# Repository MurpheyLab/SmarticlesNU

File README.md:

# SmarticlesNU

This repository includes all the hardware design and software files for the smarticle system. Examples can be found in Code/Python/Examples. See [Smarticle Tracking](https://github.com/murpheylab/SmarticleTracking) for the a python AprilTag tracking library and [SmarticleSimulation](https://github.com/asamland/SmarticleSimulation) for a PyBullet simulator of the system.  

All documentation for the python modules in this repository is available [here](https://murpheylab.github.io/SmarticlesNU/)

Installing Python Dependencies
------------

You can install pyserial and the XBee Python library using pip

    $ pip install pyserial
    $ pip install digi-xbee

Running Your First Program
-----------
Use the included `SmarticleSyncGait.py` to test your setup. You will have to modify `PORT_NAME` to match the USB port name of the local XBee connected to your computer.  

Run the the following command to execute the code and keep the python script open  
    
    $ python3 -i SmarticleSyncGait.py
    
Then you can run this command to run the smarticles for 1 minute  

    >>> timed_sync(1)

Interfacing with The Xbees
---
To Change the settings of the Base Xbee, use [DIGI XCTU](https://www.digi.com/resources/documentation/digidocs/90001526/tasks/t_download_and_install_xctu.htm)  
The Settings for the base Xbee are the default settings for 802.15.4 firmware with these changes:  
<br>
        **1.** Change mode (AP) to API Enabled  
        **2.** Change Pan ID (ID) to 1984  
        **3.** Ensure address (MY) is 0  
        **4.** Change Destination Low Address (DL) to 0xFFFF (broadcast)  
        
You can also modify these settings in a simple serial console by entering command mode. See this [guide](https://cdn.sparkfun.com/learn/materials/29/22AT%20Commands.pdf) for more information.
    
Modifying Code on The Smarticles
---
To modify the code on the smarticles themselves, you will also need to instal MiniCore into the Arduino IDE and an SI Labs driver for the CP2104 chip.  
  <br> 
    Get the CP210x Driver for your OS: [SI Labs Drivers Link](https://www.silabs.com/products/interface/usb-bridges/classic-usb-bridges/device.cp2104?q=cp2104;page=1;x6=searchHeader;q6=Software)  
    Download Arduino IDE: [Arduino IDE Link](https://www.arduino.cc/en/Main/Software)  
    Follow the instructions to install in Arduino IDE: [MiniCore Link](https://github.com/MCUdude/MiniCore#how-to-install) 
    <br>
    
After Installing all these dependencies you will have to move the files from the Code/Arduino folder into your local Arduino folder (usually found in documents)  
<br>
        **1.**  Move the programmable_smarticle folder into your Arduino directory (should be then documents/Arduino/programmable_smarticle)  
        **2.**  Move the contents of the repo Arduino/libraries folder into your local Arduino/libraries folder  
    
You will have to restart the Arduino IDE and then you should be able to open the programmable_smarticle.ino sketch and you should see PWMServo, NeoHWSerial, and Smarticle in the Sketch->Include Library file menu.

To upload the program to the smarticle, use the follow board configuration under the tools file menu:  

  | Field | Value|
|:------------:|:-------------------------------:| 
| Board        | ATmega328                      | 
| Clock        | 8MHz External                   |  
| BOD          | BOD 2.7V                        |  
| Compiler LTO | LTO Enabled                     |  
| Variant      | 328PB                           |  
| Bootloader   | Yes (UART0)                     |  
| Port         | select USB port of SI Labs Chip |

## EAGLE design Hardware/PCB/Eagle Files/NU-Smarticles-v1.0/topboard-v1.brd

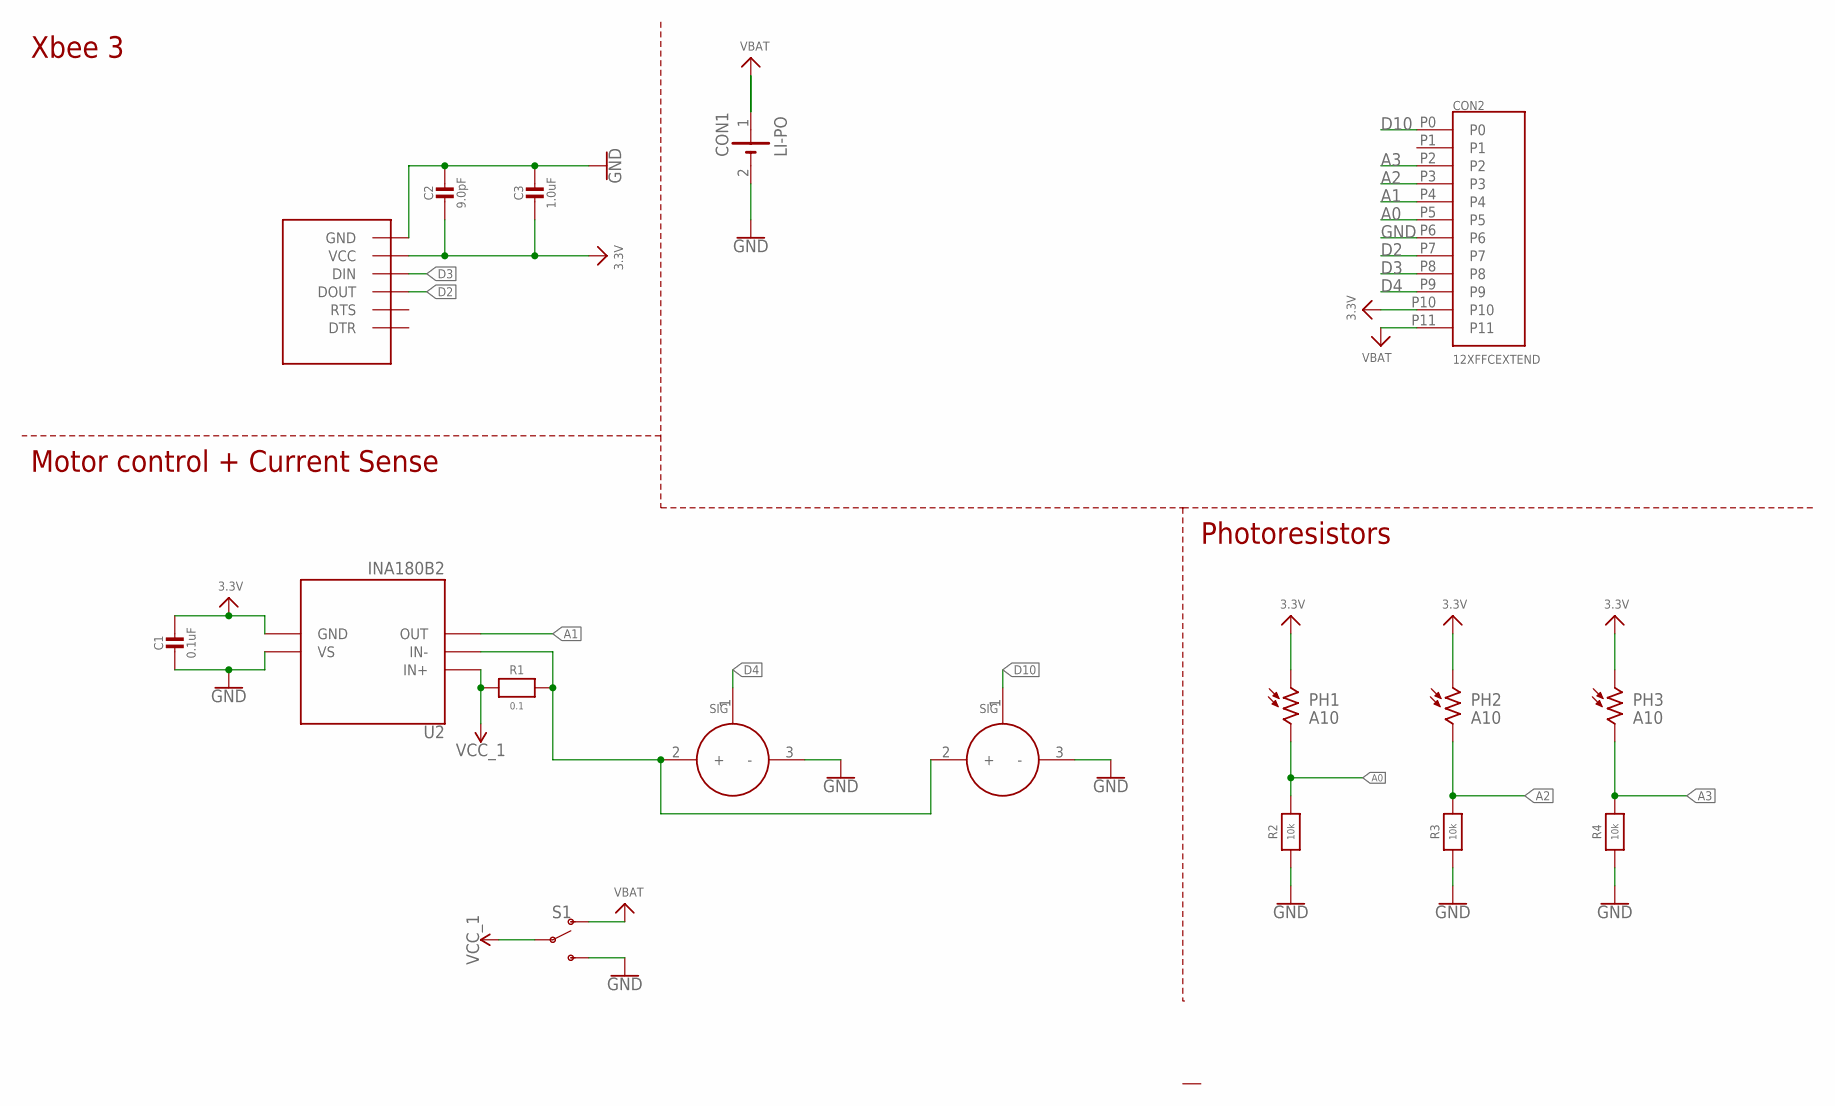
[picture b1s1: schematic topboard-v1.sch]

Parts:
C1: 0.1uF; _0603MP
C2: 9.0pF; _0603MP
C3: 1.0uF; _0603MP
CON1: LI-PO; 1X02_BATT
CON2: 12XFFCEXTEND; 15166-0117_XTEND
M1, M2: SERVO; 1X03_SERVO
PH1, PH2, PH3: A10; PHOTORESISTOR
R1: 0.1; _0603MP
R2, R3, R4: 10k; _0603MP
S1: SWITCH-SPDT-SMD-RIGHT-ANGLE; SWITCH_SPST_SMD_A
U1: XBEE3; XBEE3_MICRO
U2: INA180B2; SOT23-5

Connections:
3.3V: C1.1, C2.2, C3.2, CON2.P10, PH1.1, PH2.1, PH3.1, U1.VCC, U2.2 (GND)
A0: CON2.P5, PH1.2, R2.2
A1: CON2.P4, U2.4 (OUT)
A2: CON2.P3, PH2.2, R3.2
A3: CON2.P2, PH3.2, R4.2
D2: CON2.P7, U1.DOUT/DIO13 (DOUT)
D3: CON2.P8, U1.DIN/CONFIG/DIO14 (DIN)
D4: CON2.P9, M1.1 (SIG)
D10: CON2.P0, M2.1 (SIG)
GND: C1.2, C2.1, C3.1, CON1.2 (-), CON2.P6, M1.3 (-), M2.3 (-), R2.1, R3.1, R4.1, S1.3 (S), U1.GND1 (GND), U1.GND2 (GND), U1.GND3 (GND), U1.GND4 (GND), U1.GND5 (GND), U1.GND6 (GND), U2.5 (VS)
unnamed: M1.2 (+), M2.2 (+), R1.2, U2.3 (IN-)
VBAT: CON1.1 (+), CON2.P11, S1.1 (O)
VCC_1: R1.1, S1.2, U2.1 (IN+)

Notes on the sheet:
Xbee 3
Photoresistors
Motor control + Current Sense

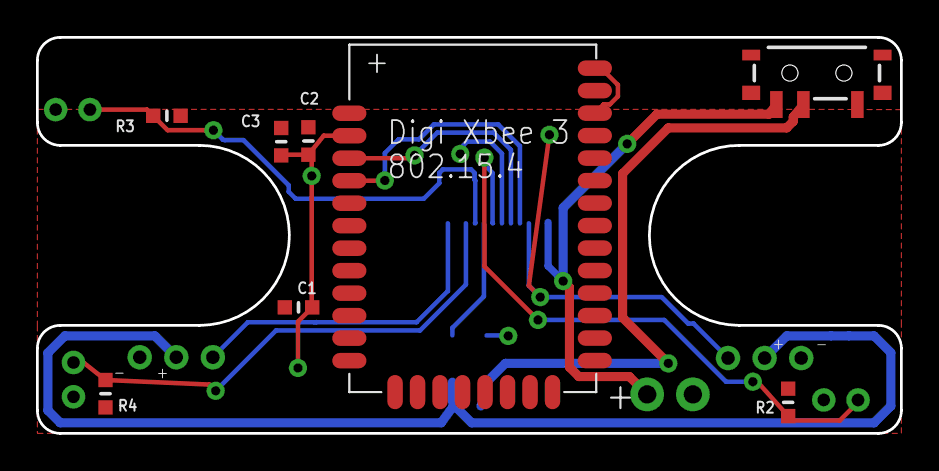
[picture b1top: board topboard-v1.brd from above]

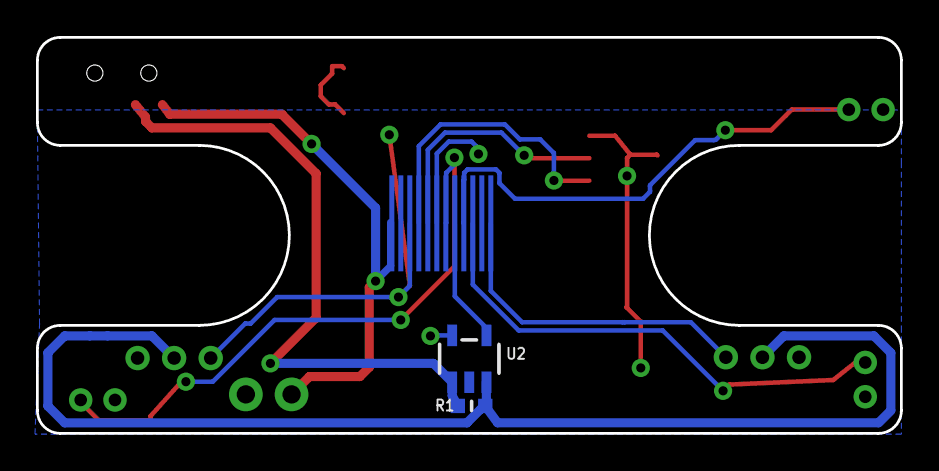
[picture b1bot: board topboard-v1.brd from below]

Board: 2 copper layers, 48.0 x 22.0 mm, 17 parts (3 on the bottom side), 13 nets.

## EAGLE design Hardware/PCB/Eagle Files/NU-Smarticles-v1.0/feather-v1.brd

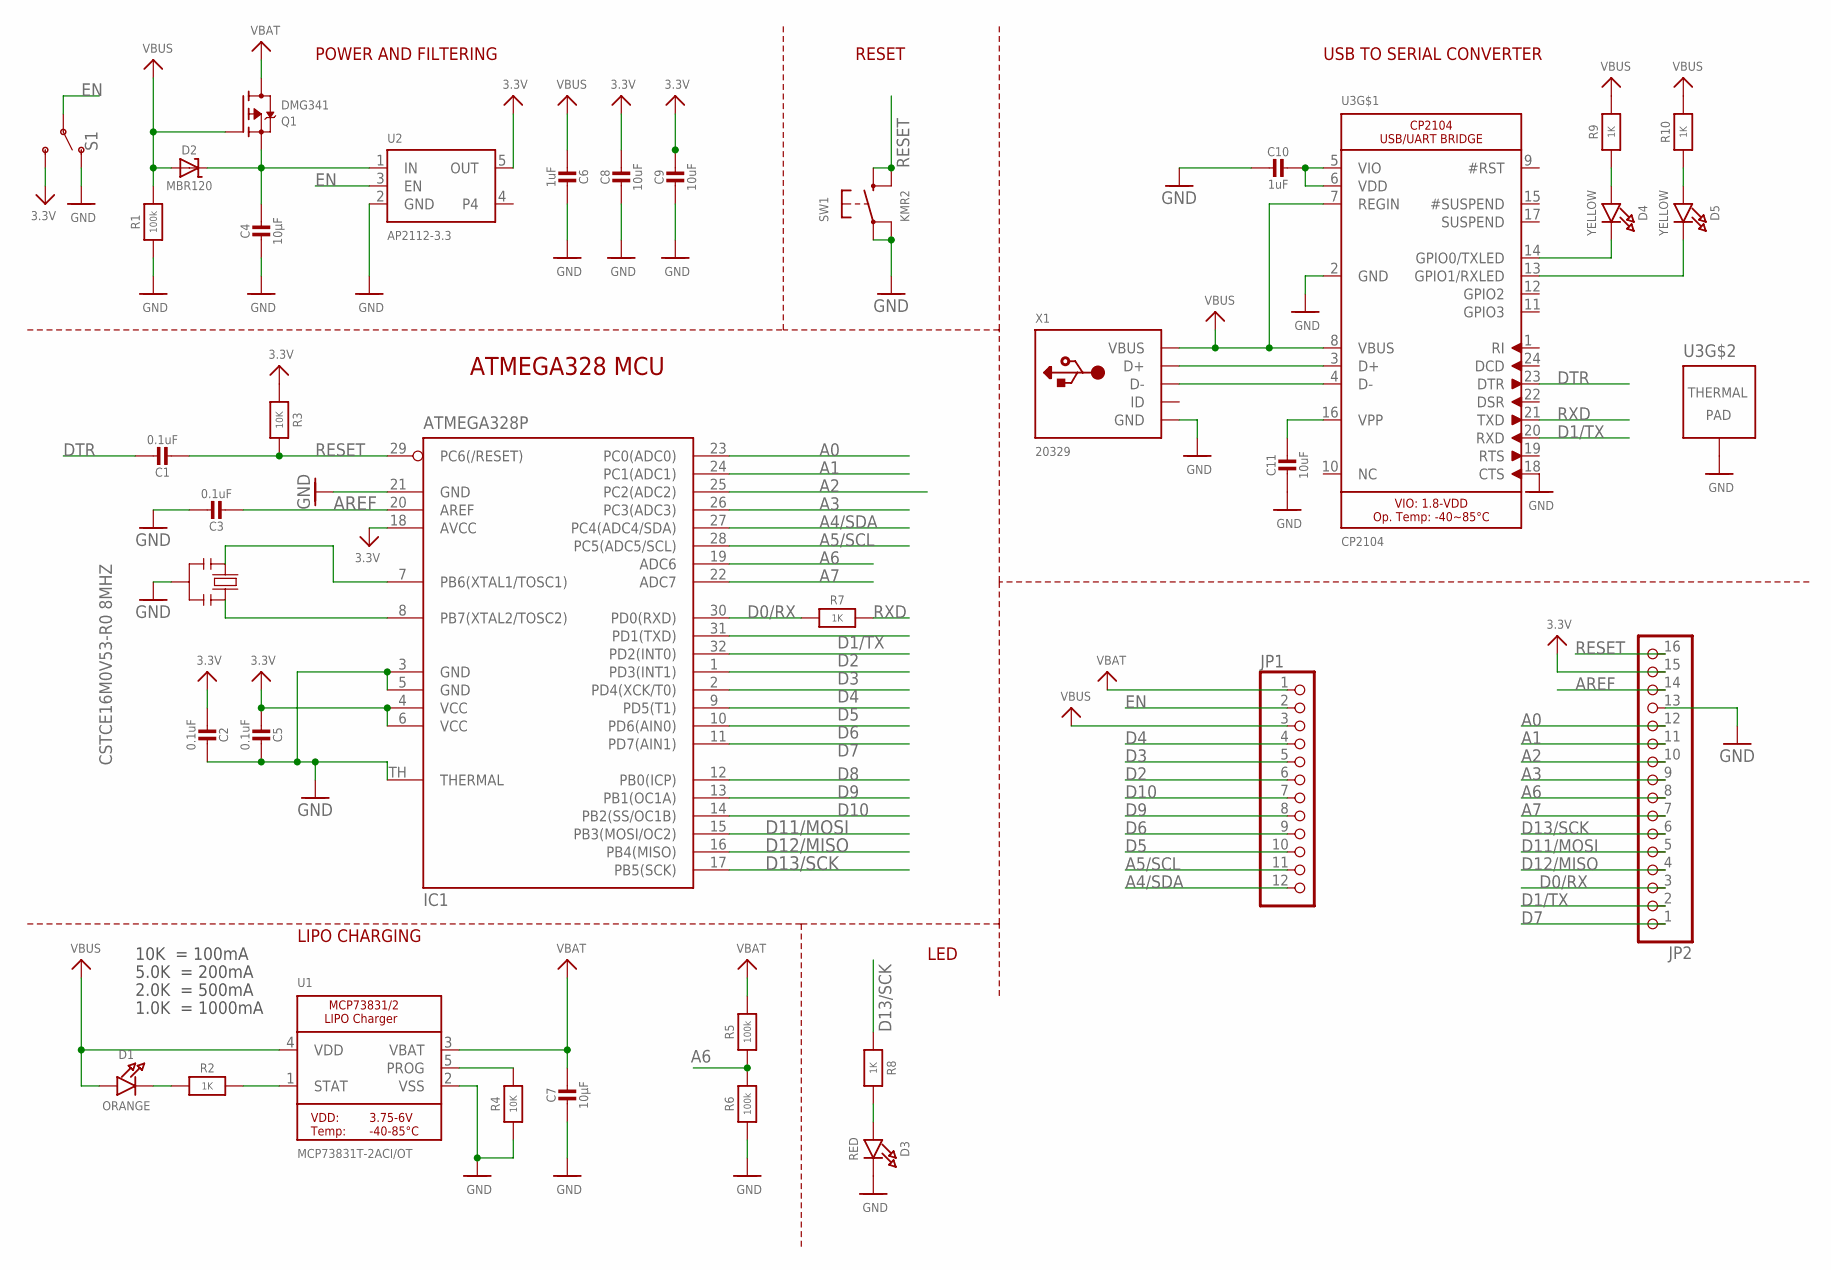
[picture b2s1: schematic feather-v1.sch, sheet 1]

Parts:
C1, C2, C3, C5: 0.1uF; _0603MP
C4, C7: 10µF; _0603MP
C6, C10: 1uF; _0603MP
C8, C9, C11: 10uF; _0603MP
D1: ORANGE; CHIPLED_0603_NOOUTLINE
D2: MBR120; SOD-523
D3: RED; CHIPLED_0603_NOOUTLINE
D4, D5: YELLOW; CHIPLED_0603_NOOUTLINE
IC1: ATMEGA328P; MLF32-TH
JP1: HEADER-1X12; 1X12_ROUND
JP2: HEADER-1X16ROUND; 1X16_ROUND
Q1: DMG341; SOT23-R
R1, R5, R6: 100k; _0603MP
R2, R7, R8, R9, R10: 1K; _0603MP
R3, R4: 10K; _0603MP
S1: SWITCH-SPDT-SMD-RIGHT-ANGLE; SWITCH_SPST_SMD_A
SW1: KMR2; BTN_KMR2_4.6X2.8
U1: MCP73831T-2ACI/OT; SOT23-5
U2: AP2112-3.3; SOT23-5
U3: CP2104; QFN24_4MM_SMSC
X1: 20329; 4UCONN_20329_V2
Y1: CSTCE16M0V53-R0 8MHZ; RESONATOR

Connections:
3.3V: C2.2, C5.2, C8.1, C9.1, IC1.4 (VCC), IC1.6 (VCC), IC1.18 (AVCC), JP2.15, R3.2, S1.3 (S), U2.5 (OUT); also elsewhere on the board
A0: IC1.23 (PC0(ADC0)), JP2.12; also elsewhere on the board
A1: IC1.24 (PC1(ADC1)), JP2.11; also elsewhere on the board
A2: IC1.25 (PC2(ADC2)), JP2.10; also elsewhere on the board
A3: IC1.26 (PC3(ADC3)), JP2.9; also elsewhere on the board
A4/SDA: IC1.27 (PC4(ADC4/SDA)), JP1.12
A5/SCL: IC1.28 (PC5(ADC5/SCL)), JP1.11
A6: IC1.19 (ADC6), JP2.8, R5.1, R6.2
A7: IC1.22 (ADC7), JP2.7
AREF: C3.2, IC1.20 (AREF), JP2.14
D0/RX: IC1.30 (PD0(RXD)), JP2.3, R7.1
D1/TX: IC1.31 (PD1(TXD)), JP2.2, U3.20 (RXD)
D2: IC1.32 (PD2(INT0)), JP1.6; also elsewhere on the board
D3: IC1.1 (PD3(INT1)), JP1.5; also elsewhere on the board
D4: IC1.2 (PD4(XCK/T0)), JP1.4; also elsewhere on the board
D5: IC1.9 (PD5(T1)), JP1.10
D6: IC1.10 (PD6(AIN0)), JP1.9
D7: IC1.11 (PD7(AIN1)), JP2.1; also elsewhere on the board
D8: IC1.12 (PB0(ICP))
D9: IC1.13 (PB1(OC1A)), JP1.8
D10: IC1.14 (PB2(SS/OC1B)), JP1.7; also elsewhere on the board
D11/MOSI: IC1.15 (PB3(MOSI/OC2)), JP2.5
D12/MISO: IC1.16 (PB4(MISO)), JP2.4
D13/SCK: IC1.17 (PB5(SCK)), JP2.6, R8.1
DTR: C1.1, U3.23 (DTR)
EN: JP1.2, S1.2, U2.3 (EN)
GND: C2.1, C3.1, C4.2, C5.1, C6.1, C7.2, C8.2, C9.2, C10.2, C11.2, D3.C, IC1.3 (GND), IC1.5 (GND), IC1.21 (GND), IC1.TH (THERMAL), JP2.13, R1.1, R4.1, R6.1, S1.1 (O), SW1.A, SW1.A' (P1), U1.2 (VSS), U2.2 (GND), U3.2 (GND), U3.18 (CTS), U3.THERM (TP), X1.BASE@1 (GND), X1.BASE@2 (GND), X1.GND, X1.SPRT@1 (GND), X1.SPRT@2 (GND), X1.SPRT@3 (GND), X1.SPRT@4 (GND), Y1.2; also elsewhere on the board
unnamed: D1.C, R2.1
unnamed: U3.3 (D+), X1.D+
unnamed: R2.2, U1.1 (STAT)
unnamed: R4.2, U1.5 (PROG)
unnamed: D3.A, R8.2
unnamed: U3.4 (D-), X1.D-
unnamed: C4.1, D2.K (C), Q1.2 (S), U2.1 (IN)
unnamed: D5.A, R10.1
unnamed: D4.A, R9.1
unnamed: C10.1, U3.5 (VIO), U3.6 (VDD)
unnamed: C11.1, U3.16 (VPP)
RESET: C1.2, IC1.29 (PC6(/RESET)), JP2.16, R3.1, SW1.B (S), SW1.B' (S1)
RXD: R7.2, U3.21 (TXD)
RXLED: D5.C, U3.13 (GPIO1/RXLED)
TXLED: D4.C, U3.14 (GPIO0/TXLED)
VBAT: C7.1, JP1.1, Q1.3 (D), R5.2, U1.3 (VBAT); also elsewhere on the board
VBUS: C6.2, D1.A, D2.A, JP1.3, Q1.1 (G), R1.2, R9.2, R10.2, U1.4 (VDD), U3.7 (REGIN), U3.8 (VBUS), X1.VBUS
XTAL1: IC1.8 (PB7(XTAL2/TOSC2)), Y1.3
XTAL2: IC1.7 (PB6(XTAL1/TOSC1)), Y1.1

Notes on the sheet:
POWER AND FILTERING
RESET
10K = 100mA
5.0K = 200mA
2.0K = 500mA
1.0K = 1000mA
USB TO SERIAL CONVERTER
LIPO CHARGING
LED
ATMEGA328 MCU

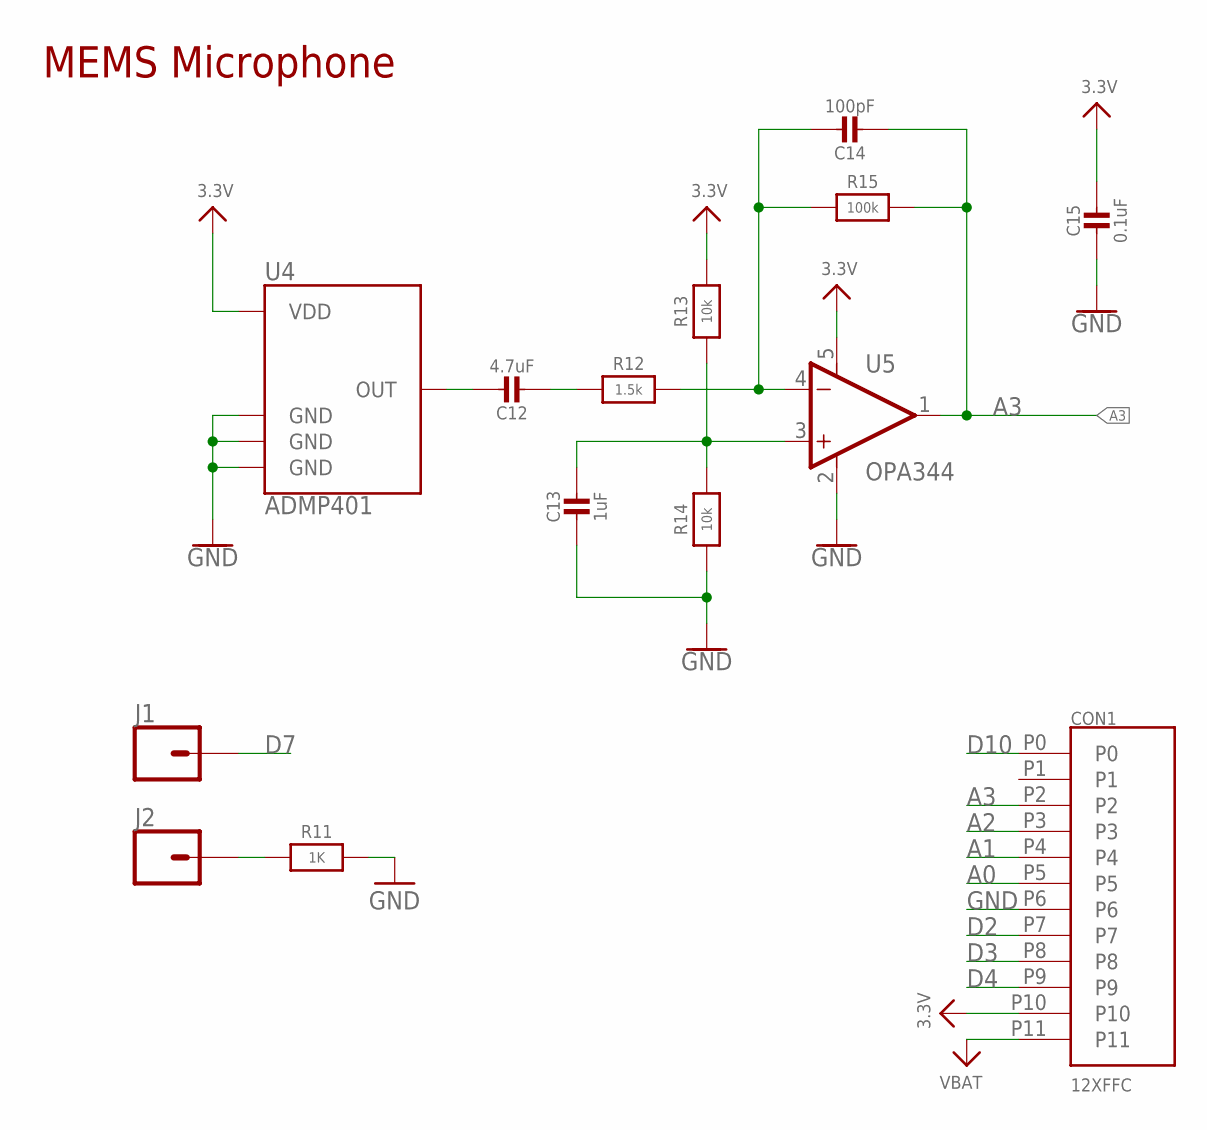
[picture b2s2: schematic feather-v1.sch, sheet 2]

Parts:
C12: 4.7uF; _0603MP
C13: 1uF; _0603MP
C14: 100pF; _0603MP
C15: 0.1uF; _0603MP
CON1: 12XFFC; 15166-0117
J1, J2: CONN_01PTH_NO_SILK_YES_STOP; 1X01_NO_SILK
R11: 1K; _0603MP
R12: 1.5k; _0603MP
R13, R14: 10k; _0603MP
R15: 100k; _0603MP
U4: ADMP401
U5: OPA344; SOT23-5

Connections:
3.3V: C15.1, CON1.P10, R13.2, U4.5 (VDD), U5.5 (V+); also elsewhere on the board
A0: CON1.P5; also elsewhere on the board
A1: CON1.P4; also elsewhere on the board
A2: CON1.P3; also elsewhere on the board
A3: C14.2, CON1.P2, R15.2, U5.1 (OUT); also elsewhere on the board
D2: CON1.P7; also elsewhere on the board
D3: CON1.P8; also elsewhere on the board
D4: CON1.P9; also elsewhere on the board
D7: J1.1; also elsewhere on the board
D10: CON1.P0; also elsewhere on the board
GND: C13.2, C15.2, CON1.P6, R11.2, R14.1, U4.2 (GND), U4.4 (GND), U4.6 (GND), U5.2 (V-); also elsewhere on the board
unnamed: J2.1, R11.1
unnamed: C12.1, U4.1 (OUT)
unnamed: C14.1, R12.2, R15.1, U5.4 (-IN)
unnamed: C12.2, R12.1
unnamed: C13.1, R13.1, R14.2, U5.3 (+IN)
VBAT: CON1.P11; also elsewhere on the board

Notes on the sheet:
MEMS Microphone

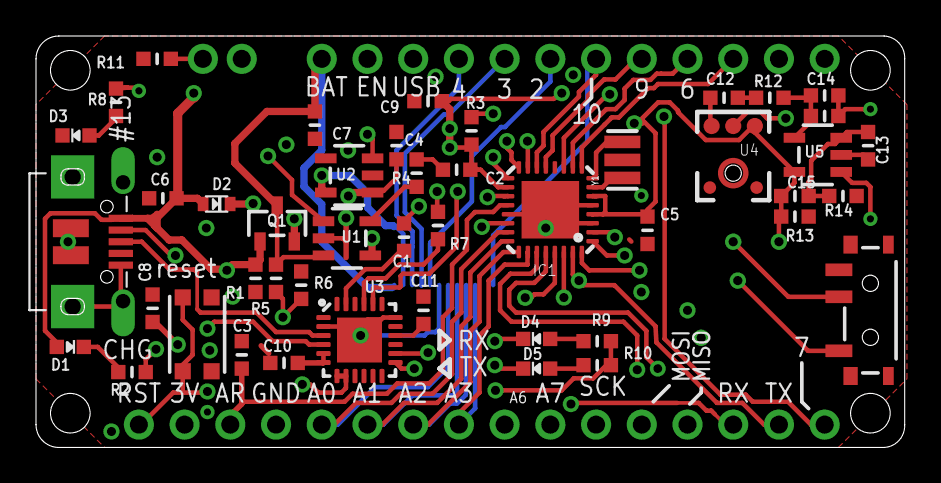
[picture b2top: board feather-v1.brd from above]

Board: 4 copper layers, 48.3 x 22.9 mm, 51 parts (1 on the bottom side), 50 nets.

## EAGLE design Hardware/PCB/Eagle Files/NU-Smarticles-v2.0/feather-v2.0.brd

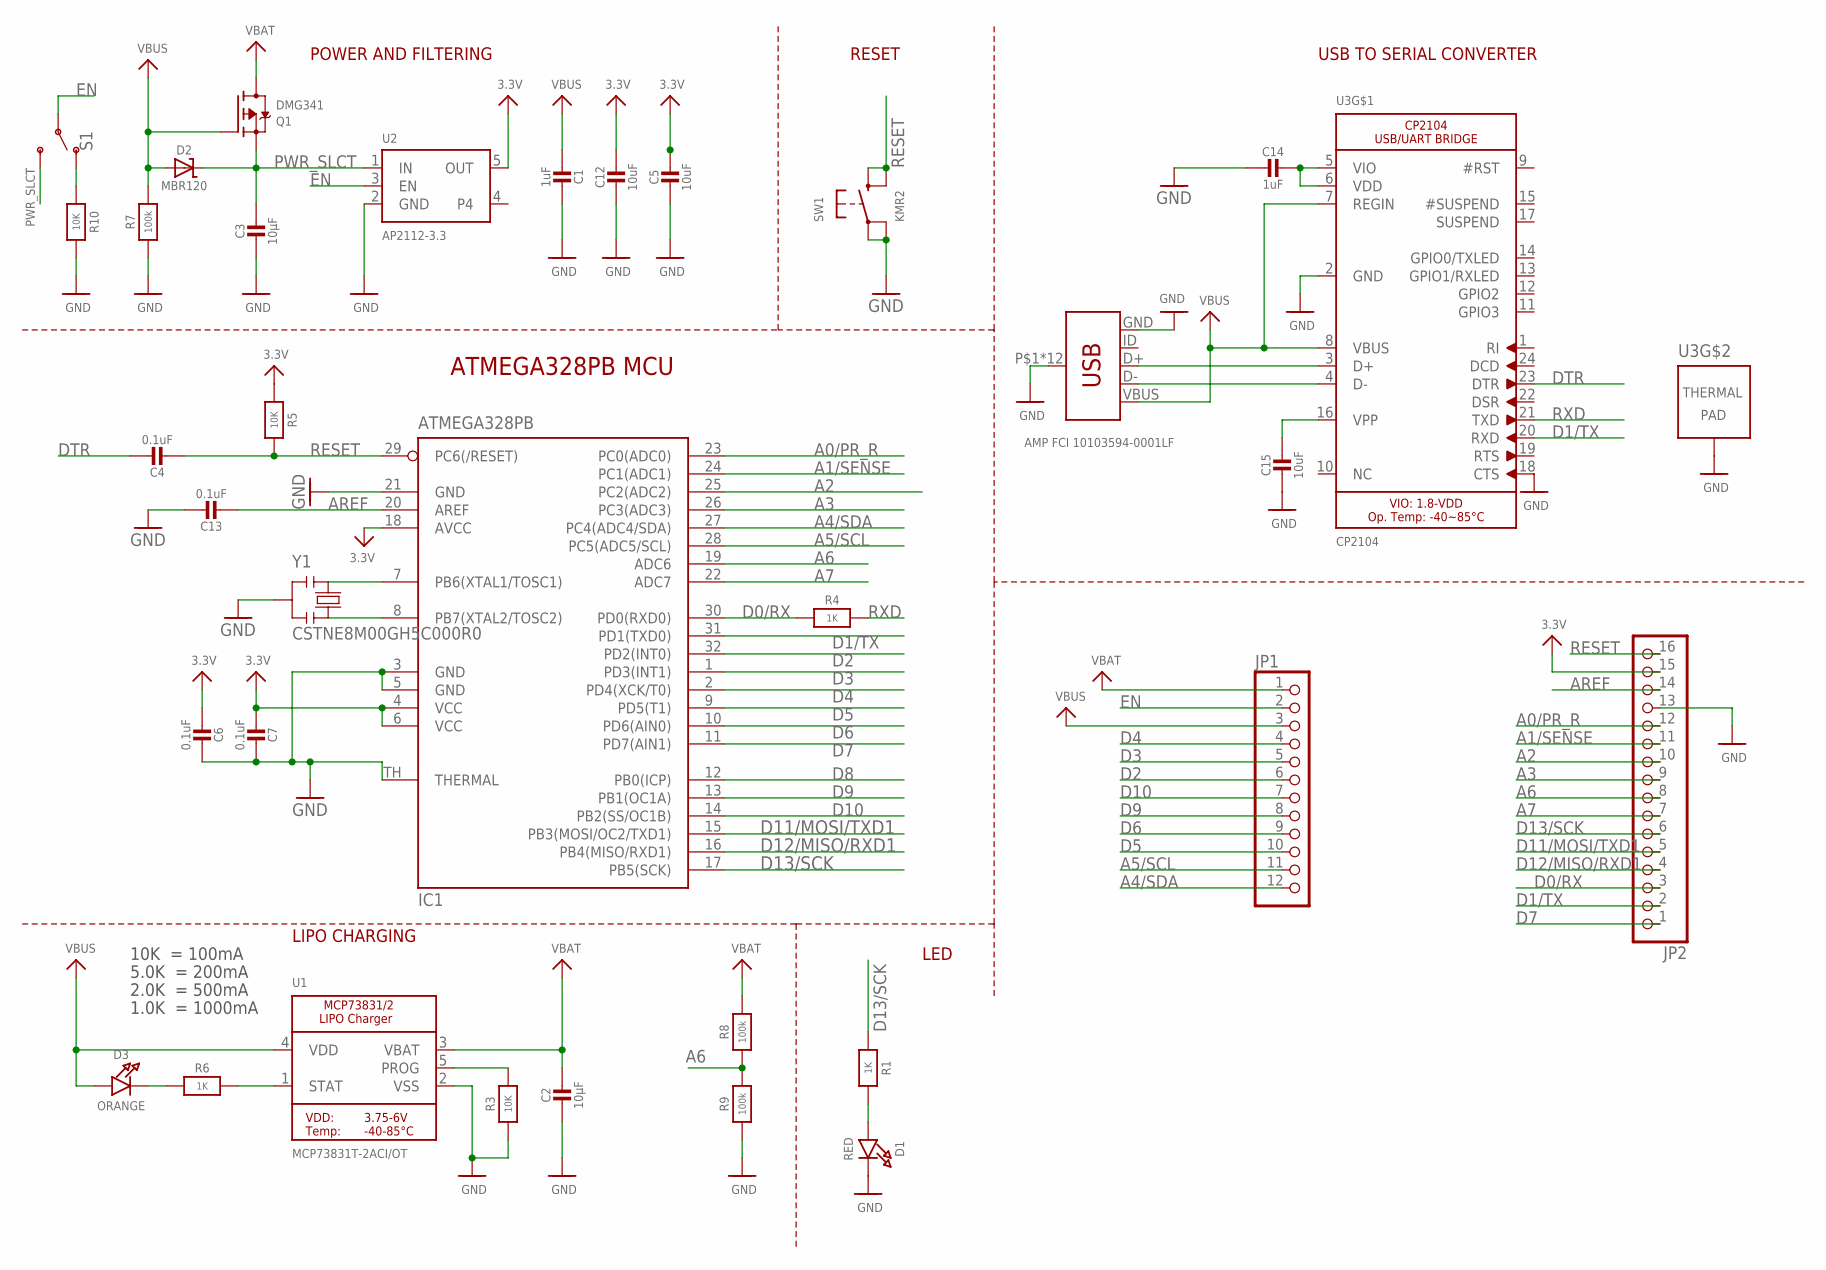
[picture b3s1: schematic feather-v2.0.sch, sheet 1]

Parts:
C1, C14: 1uF; _0603MP
C2, C3: 10µF; _0603MP
C4, C6, C7, C13: 0.1uF; _0603MP
C5, C12, C15: 10uF; _0603MP
D1: RED; CHIPLED_0603_NOOUTLINE
D2: MBR120; SOD-323
D3: ORANGE; CHIPLED_0603_NOOUTLINE
IC1: ATMEGA328PB; MLF32-TH
JP1: HEADER-1X12; 1X12_ROUND
JP2: HEADER-1X16ROUND; 1X16_ROUND
Q1: DMG341; SOT23-R
R1, R4, R6: 1K; _0603MP
R3, R5, R10: 10K; _0603MP
R7, R8, R9: 100k; _0603MP
S1: SWITCH-SPDT-SMD-RIGHT-ANGLE; SWITCH_SPST_SMD_A
SW1: KMR2; BTN_KMR2_4.6X2.8
U1: MCP73831T-2ACI/OT; SOT23-5
U2: AP2112-3.3; SOT23-5
U3: CP2104; QFN24_4MM_SMSC
X1: AMP FCI 10103594-0001LF; USB-MICROB-PTH
Y1: CSTNE8M00GH5C000R0; RESONATOR

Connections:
3.3V: C5.1, C6.2, C7.2, C12.1, IC1.4 (VCC), IC1.6 (VCC), IC1.18 (AVCC), JP2.15, R5.2, U2.5 (OUT); also elsewhere on the board
A0/PR_R: IC1.23 (PC0(ADC0)), JP2.12; also elsewhere on the board
A1/SENSE: IC1.24 (PC1(ADC1)), JP2.11; also elsewhere on the board
A2: IC1.25 (PC2(ADC2)), JP2.10; also elsewhere on the board
A3: IC1.26 (PC3(ADC3)), JP2.9; also elsewhere on the board
A4/SDA: IC1.27 (PC4(ADC4/SDA)), JP1.12; also elsewhere on the board
A5/SCL: IC1.28 (PC5(ADC5/SCL)), JP1.11; also elsewhere on the board
A6: IC1.19 (ADC6), JP2.8, R8.1, R9.2
A7: IC1.22 (ADC7), JP2.7; also elsewhere on the board
AREF: C13.2, IC1.20 (AREF), JP2.14
D0/RX: IC1.30 (PD0(RXD0)), JP2.3, R4.1
D1/TX: IC1.31 (PD1(TXD0)), JP2.2, U3.20 (RXD)
D2: IC1.32 (PD2(INT0)), JP1.6
D3: IC1.1 (PD3(INT1)), JP1.5
D4: IC1.2 (PD4(XCK/T0)), JP1.4
D5: IC1.9 (PD5(T1)), JP1.10
D6: IC1.10 (PD6(AIN0)), JP1.9
D7: IC1.11 (PD7(AIN1)), JP2.1; also elsewhere on the board
D8: IC1.12 (PB0(ICP))
D9: IC1.13 (PB1(OC1A)), JP1.8; also elsewhere on the board
D10: IC1.14 (PB2(SS/OC1B)), JP1.7; also elsewhere on the board
D11/MOSI/TXD1: IC1.15 (PB3(MOSI/OC2/TXD1)), JP2.5; also elsewhere on the board
D12/MISO/RXD1: IC1.16 (PB4(MISO/RXD1)), JP2.4; also elsewhere on the board
D13/SCK: IC1.17 (PB5(SCK)), JP2.6, R1.1
DTR: C4.1, U3.23 (DTR)
EN: JP1.2, S1.2, U2.3 (EN)
GND: C1.1, C2.2, C3.2, C5.2, C6.1, C7.1, C12.2, C13.1, C14.2, C15.2, D1.C, IC1.3 (GND), IC1.5 (GND), IC1.21 (GND), IC1.TH (THERMAL), JP2.13, R3.1, R7.1, R9.1, R10.1, SW1.A, SW1.A' (P1), U1.2 (VSS), U2.2 (GND), U3.2 (GND), U3.18 (CTS), U3.THERM (TP), X1.GND, X1.P$1 (SHIELD), X1.P$2 (SHIELD), X1.P$3 (SHIELD), X1.P$4 (SHIELD), X1.P$6 (SHIELD), X1.P$8 (SHIELD), X1.P$10 (SHIELD), X1.P$12 (SHIELD), X1.SHEILD2 (SHIELD), X1.SHIELD, X1.SHIELD3 (SHIELD), X1.SHIELD4 (SHIELD), Y1.2; also elsewhere on the board
unnamed: D3.C, R6.1
unnamed: U3.3 (D+), X1.D+
unnamed: R6.2, U1.1 (STAT)
unnamed: R3.2, U1.5 (PROG)
unnamed: D1.A, R1.2
unnamed: U3.4 (D-), X1.D-
unnamed: R10.2, S1.1 (O)
unnamed: IC1.8 (PB7(XTAL2/TOSC2)), Y1.3
unnamed: C14.1, U3.5 (VIO), U3.6 (VDD)
unnamed: IC1.7 (PB6(XTAL1/TOSC1)), Y1.1
unnamed: C15.1, U3.16 (VPP)
PWR_SLCT: C3.1, D2.C, Q1.2 (S), S1.3 (S), U2.1 (IN)
RESET: C4.2, IC1.29 (PC6(/RESET)), JP2.16, R5.1, SW1.B (S), SW1.B' (S1)
RXD: R4.2, U3.21 (TXD)
VBAT: C2.1, JP1.1, Q1.3 (D), R8.2, U1.3 (VBAT); also elsewhere on the board
VBUS: C1.2, D2.A, D3.A, JP1.3, Q1.1 (G), R7.2, U1.4 (VDD), U3.7 (REGIN), U3.8 (VBUS), X1.VBUS

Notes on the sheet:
POWER AND FILTERING
RESET
10K = 100mA
5.0K = 200mA
2.0K = 500mA
1.0K = 1000mA
USB TO SERIAL CONVERTER
LIPO CHARGING
LED
ATMEGA328PB MCU

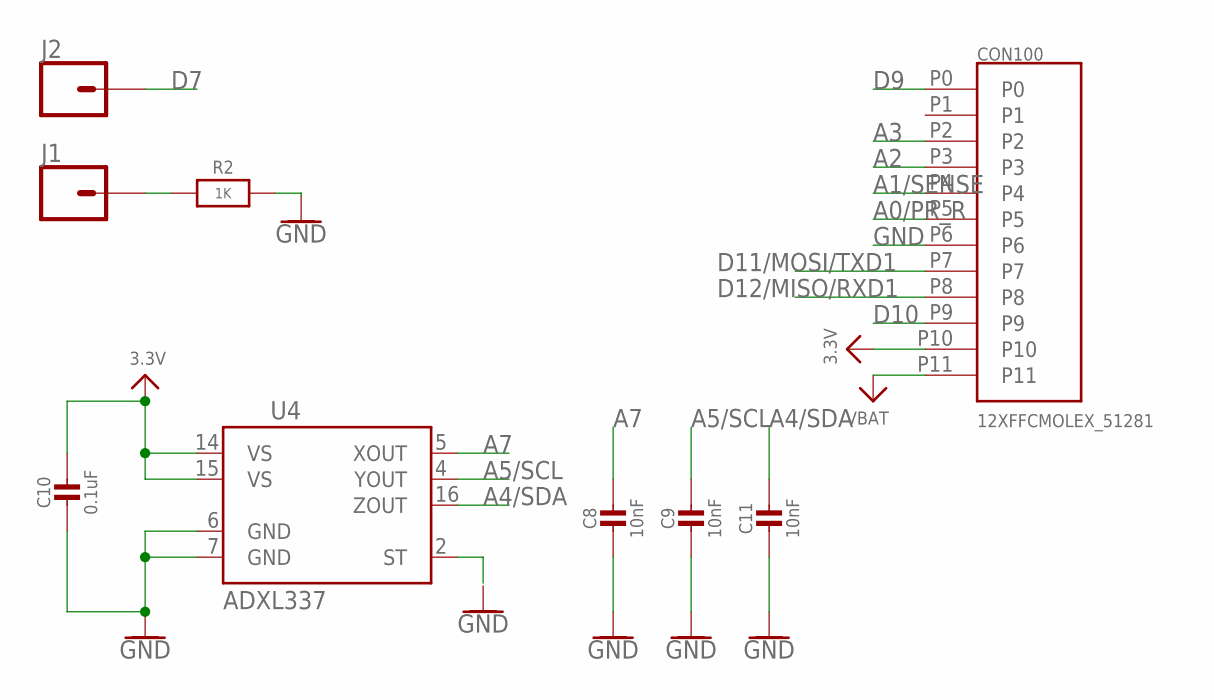
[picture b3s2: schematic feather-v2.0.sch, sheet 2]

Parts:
C8, C9, C11: 10nF; _0603MP
C10: 0.1uF; _0603MP
CON100: 12XFFCMOLEX_51281; MOLEX_51281-1294
J1, J2: CONN_01PTH_NO_SILK_YES_STOP; 1X01_NO_SILK
R2: 1K; _0603MP
U4: ADXL337; LFCSP_LQ-16

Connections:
3.3V: C10.1, CON100.P10, U4.14 (VS), U4.15 (VS); also elsewhere on the board
A0/PR_R: CON100.P5; also elsewhere on the board
A1/SENSE: CON100.P4; also elsewhere on the board
A2: CON100.P3; also elsewhere on the board
A3: CON100.P2; also elsewhere on the board
A4/SDA: C11.1, U4.16 (ZOUT); also elsewhere on the board
A5/SCL: C9.1, U4.4 (YOUT); also elsewhere on the board
A7: C8.1, U4.5 (XOUT); also elsewhere on the board
D7: J2.1; also elsewhere on the board
D9: CON100.P0; also elsewhere on the board
D10: CON100.P9; also elsewhere on the board
D11/MOSI/TXD1: CON100.P7; also elsewhere on the board
D12/MISO/RXD1: CON100.P8; also elsewhere on the board
GND: C8.2, C9.2, C10.2, C11.2, CON100.P6, R2.2, U4.6 (GND), U4.7 (GND); also elsewhere on the board
unnamed: J1.1, R2.1
VBAT: CON100.P11; also elsewhere on the board

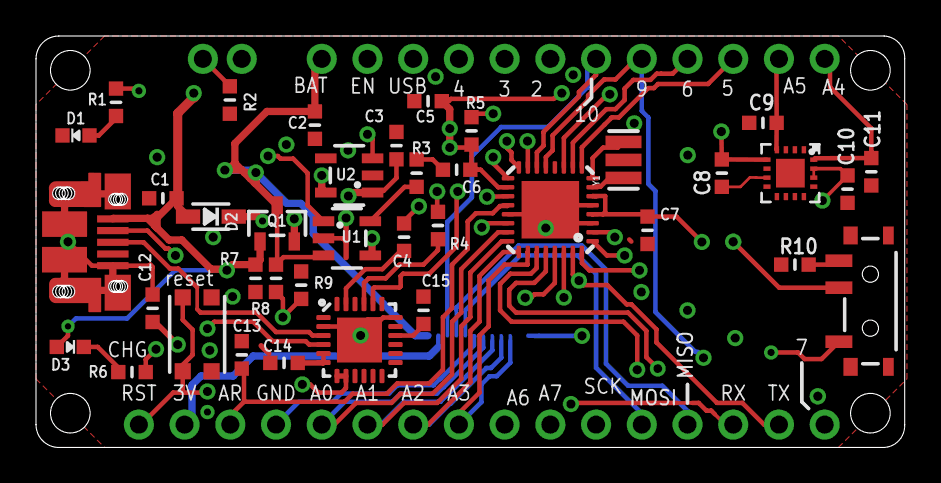
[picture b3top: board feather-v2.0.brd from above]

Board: 4 copper layers, 48.3 x 22.9 mm, 43 parts (1 on the bottom side), 43 nets.

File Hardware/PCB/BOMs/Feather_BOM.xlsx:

Item# | Ref Des | Qty | Manufacturer | Mfg Part no. | Package | Description/ Value | Type
1 | C8, C9, C11 | 3 |  |  | 0603 | 10nF | SMD
2 | C4, C6, C7, C10, C13 | 5 |  |  | 0603 | 0.1 uF | SMD
3 | C1,C14 | 2 |  |  | 0603 | 1.0uF | SMD
4 | C2,C3,C5,C12,C15 | 5 |  |  | 0603 | 10uF | SMD
5 | CON1 | 1 | Amphenol ICC | 10103594-0001LF |  | Micro B USB Connectors | SMD
6 | CON100 | 1 | Molex | 512811294 |  |  | SMD
7 | D1 | 1 |  |  | CHIP-LED 0603 | Red LED | SMD
8 | D2 | 1 | Diodes Inc. | SDM100K30L-7 | SOD-323 | Schottky Diode | SMD
9 | D3 | 1 |  |  | CHIP-LED 0603 | Orange LED | SMD
10 | Q1 | 1 | Didoes Inc. | DMG3418L | SOT23-R | P-Channel Mosfet | SMD
11 | R1, R2, R4, R6 | 4 |  |  | 0603 | 1K | SMD
12 | R3, R5, R10 | 3 |  |  | 0603 | 10k | SMD
13 | R7, R8, R9 | 3 |  |  | 0603 | 100k | SMD
14 | S1 | 1 | C&K | KMR231NG LFS |  | SMT Tact Switches | SMD
15 | S2 | 1 | C&K | PCM12SMTR |  | Single Pole, Double Throw (SPDT) Switch | SMD
16 | U1 | 1 | Microchip Technology | ﻿MCP73831T-2DCI/OT | SOT23-5 | MCP73831/2 LIPO Charger | SMD
17 | U2 | 1 | Diodes Inc. | ﻿AP2112K-3.3 | SOT23-5 | SOT23-5 Fixed Voltage Regulators | SMD
18 | U3 | 1 | Silicon Labs | ﻿CP2104 | QFN24_4MM_SMSC | CP2104 - USB to UART Bridge | SMD
19 | U4 | 1 | Microchip Technology | ATmega328PB-MUR | 32VFQFN | IC MCU 8BIT 32KB FLASH 32VFQFN | SMD
20 | U5 | 1 | Analog Devices | ADXL337BCPZ-RL | LFCSP_LQ-16 | ADXL337 Low Power 3-Axis ¬±3 g Accelerometer with Analog Output. | SMD
21 | Y1 | 1 | Murata | CSTNE8M00GH5C000R0 |  | 8mhz resonator | SMD

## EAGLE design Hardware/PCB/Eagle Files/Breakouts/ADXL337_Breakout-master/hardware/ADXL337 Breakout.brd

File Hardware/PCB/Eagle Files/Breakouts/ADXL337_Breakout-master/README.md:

ADXL337 Breakout
================

[   
*Triple Axis Accelerometer Breakout-ADXL337 (SEN-12786)*](https://www.sparkfun.com/products/12786)

A Breakout Board for the ADXL337 Low Power 3-Axis ±3 g Accelerometer with Analog Output.

Repository Contents
-------------------
* **/Hardware** - All Eagle design files (.brd, .sch)
* **/Production** - Test bed files and production panel files
* **/Firmware** - All Arduino sketches for this product

License Information
-------------------
The hardware is released under [Creative Commons ShareAlike 4.0 International](https://creativecommons.org/licenses/by-sa/4.0/).

Distributed as-is; no warranty is given.

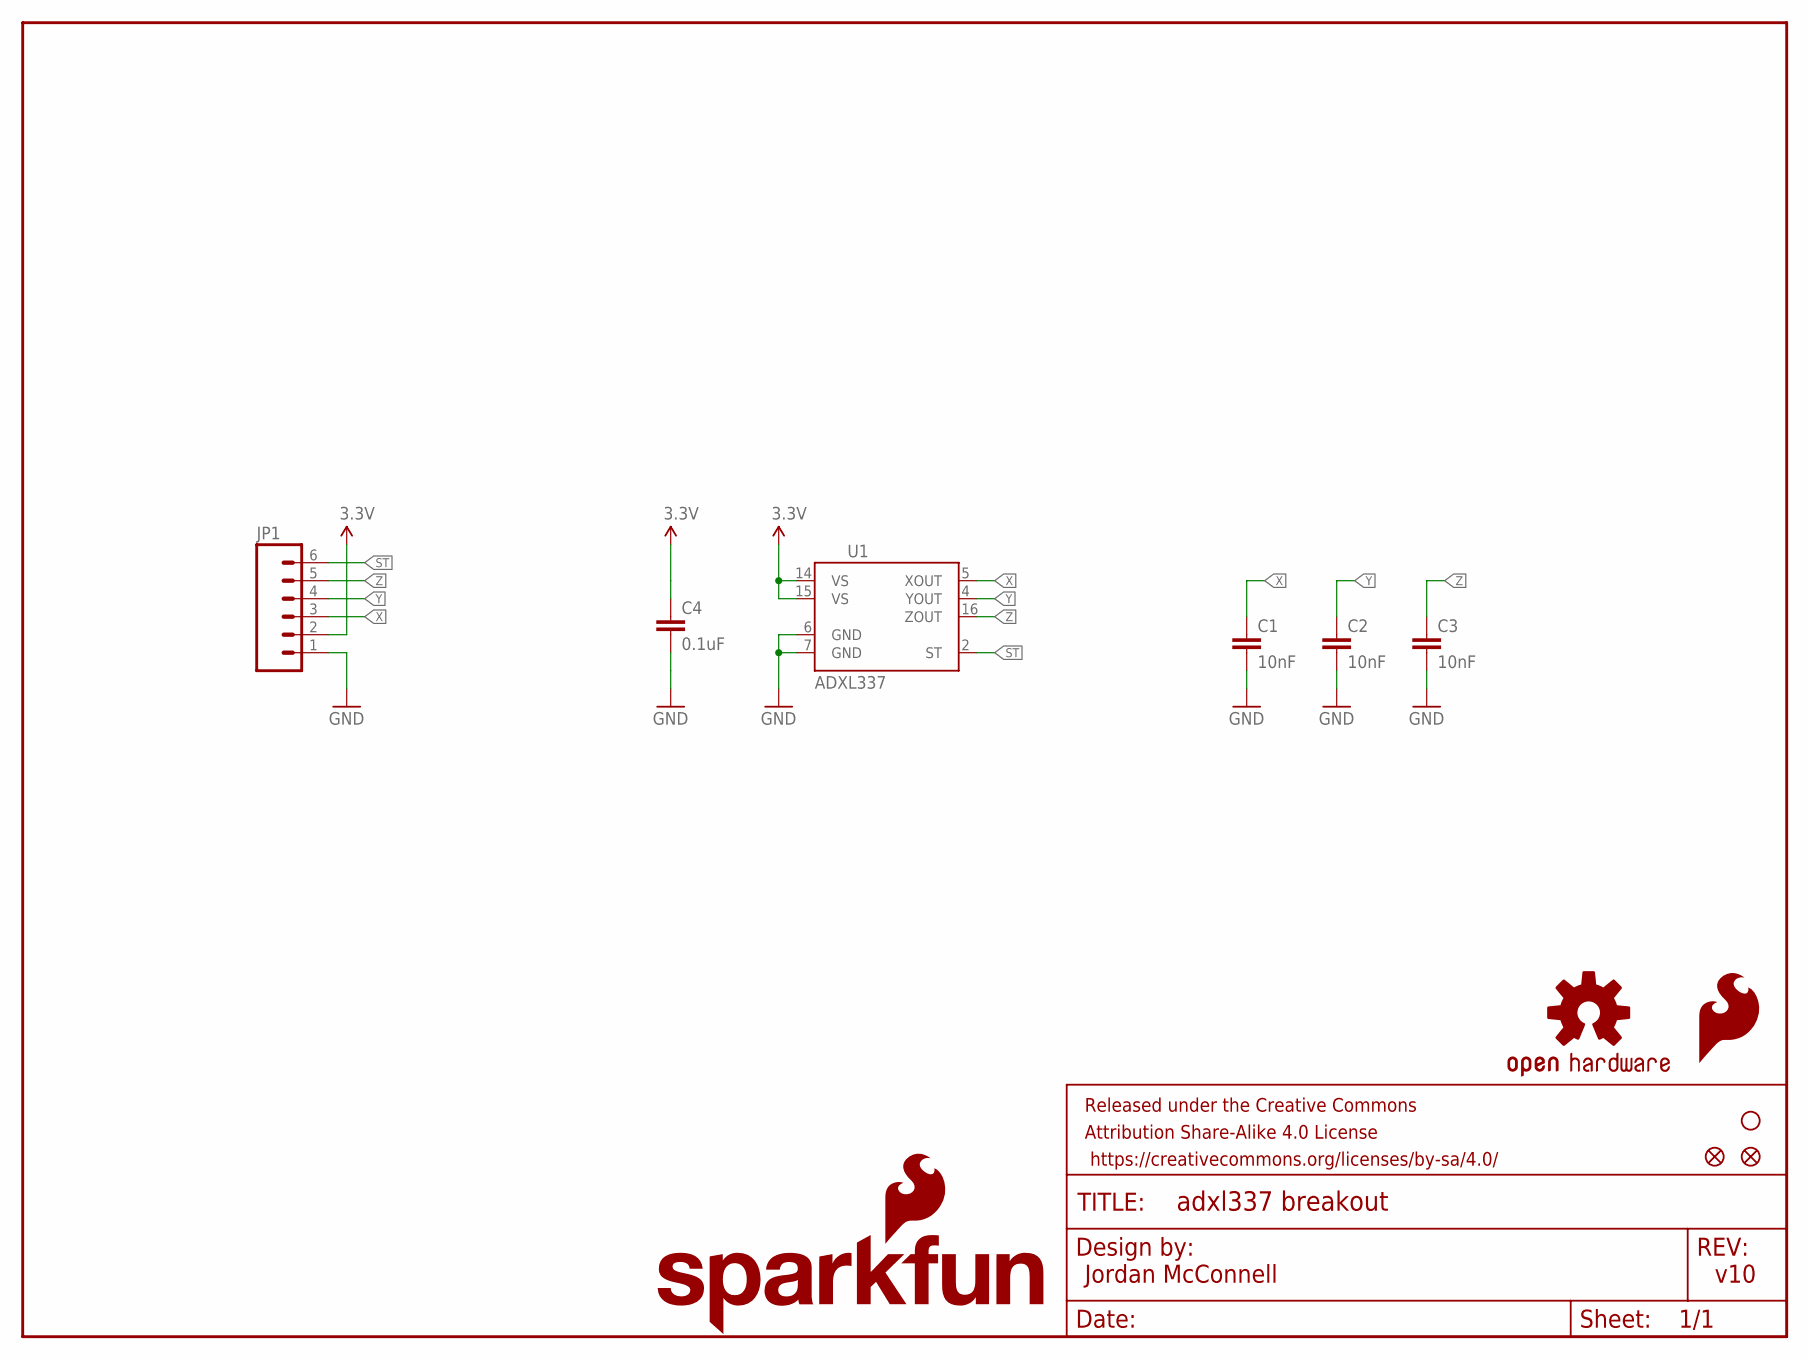
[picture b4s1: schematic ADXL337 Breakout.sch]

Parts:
C1, C2, C3: 10nF; 0603-CAP
C4: 0.1uF; 0603-CAP
FID1, FID2: FIDUCIAL1X2; FIDUCIAL-1X2
FRAME1: FRAME-LETTER; CREATIVE_COMMONS
JP1: M06SIP; 1X06
LOGO1: SFE_LOGO_FLAME.1_INCH; SFE_LOGO_FLAME_.1
LOGO2: OSHW-LOGOS; OSHW-LOGO-S
LOGO3: SFE_LOGO_NAME_FLAME.1_INCH; SFE_LOGO_NAME_FLAME_.1
STANDOFF1: STAND-OFF
U1: ADXL337; LFCSP_LQ-16

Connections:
3.3V: C4.1, JP1.2, U1.14 (VS), U1.15 (VS)
GND: C1.2, C2.2, C3.2, C4.2, JP1.1, U1.6 (GND), U1.7 (GND)
ST: JP1.6, U1.2 (ST)
X: C1.1, JP1.3, U1.5 (XOUT)
Y: C2.1, JP1.4, U1.4 (YOUT)
Z: C3.1, JP1.5, U1.16 (ZOUT)

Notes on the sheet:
Jordan McConnell
v10

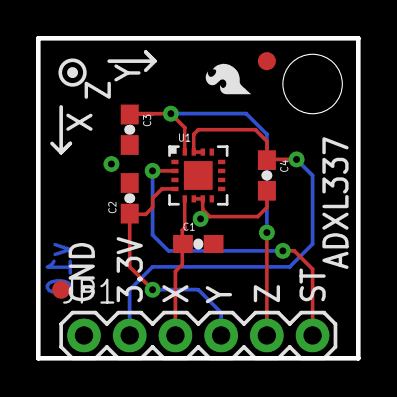
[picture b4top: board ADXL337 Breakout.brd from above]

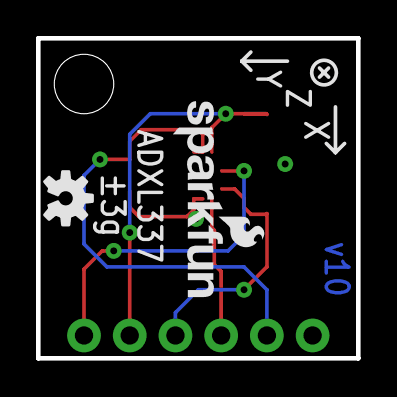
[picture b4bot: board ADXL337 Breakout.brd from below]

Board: 2 copper layers, 17.8 x 17.8 mm, 13 parts (2 on the bottom side), 6 nets.

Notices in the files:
parts and their libraries:
SparkFun-Aesthetics: Licensing: Creative Commons ShareAlike 4.0 International - https://creativecommons.org/licenses/by-sa/4.0
SparkFun-Aesthetics: Released under the Creative Commons Attribution Share-Alike 4.0 License
SparkFun-Aesthetics: Released under the Creative Commons
